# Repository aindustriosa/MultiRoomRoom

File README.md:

Multi Room Room é un sistema de audio inalámbrico multi-habitación baseado en ESP32, Squeezelite[(1)](#1-httpsgithubcomsle118squeezelite-esp32) e Lyrion[(2)](#2-httpsgithubcomlms-communityslimserver). Permite a implementación dun sistema de fío musical inalámbrico de baixo custo e con tecnoloxías abertas. Neste repositorio atópanse as listas de materiais, deseños de placas electrónicas e caixas así como as instruccións para a posta en marcha do sistema.

## Documentación

[Documentación en galego](./docs/gl/INDICE.md)

Documentation in English (In progress)

## Referencias

#### [(1) https://github.com/sle118/squeezelite-esp32](https://github.com/sle118/squeezelite-esp32)

#### [(2) https://github.com/lms-community/slimserver](https://github.com/lms-community/slimserver)

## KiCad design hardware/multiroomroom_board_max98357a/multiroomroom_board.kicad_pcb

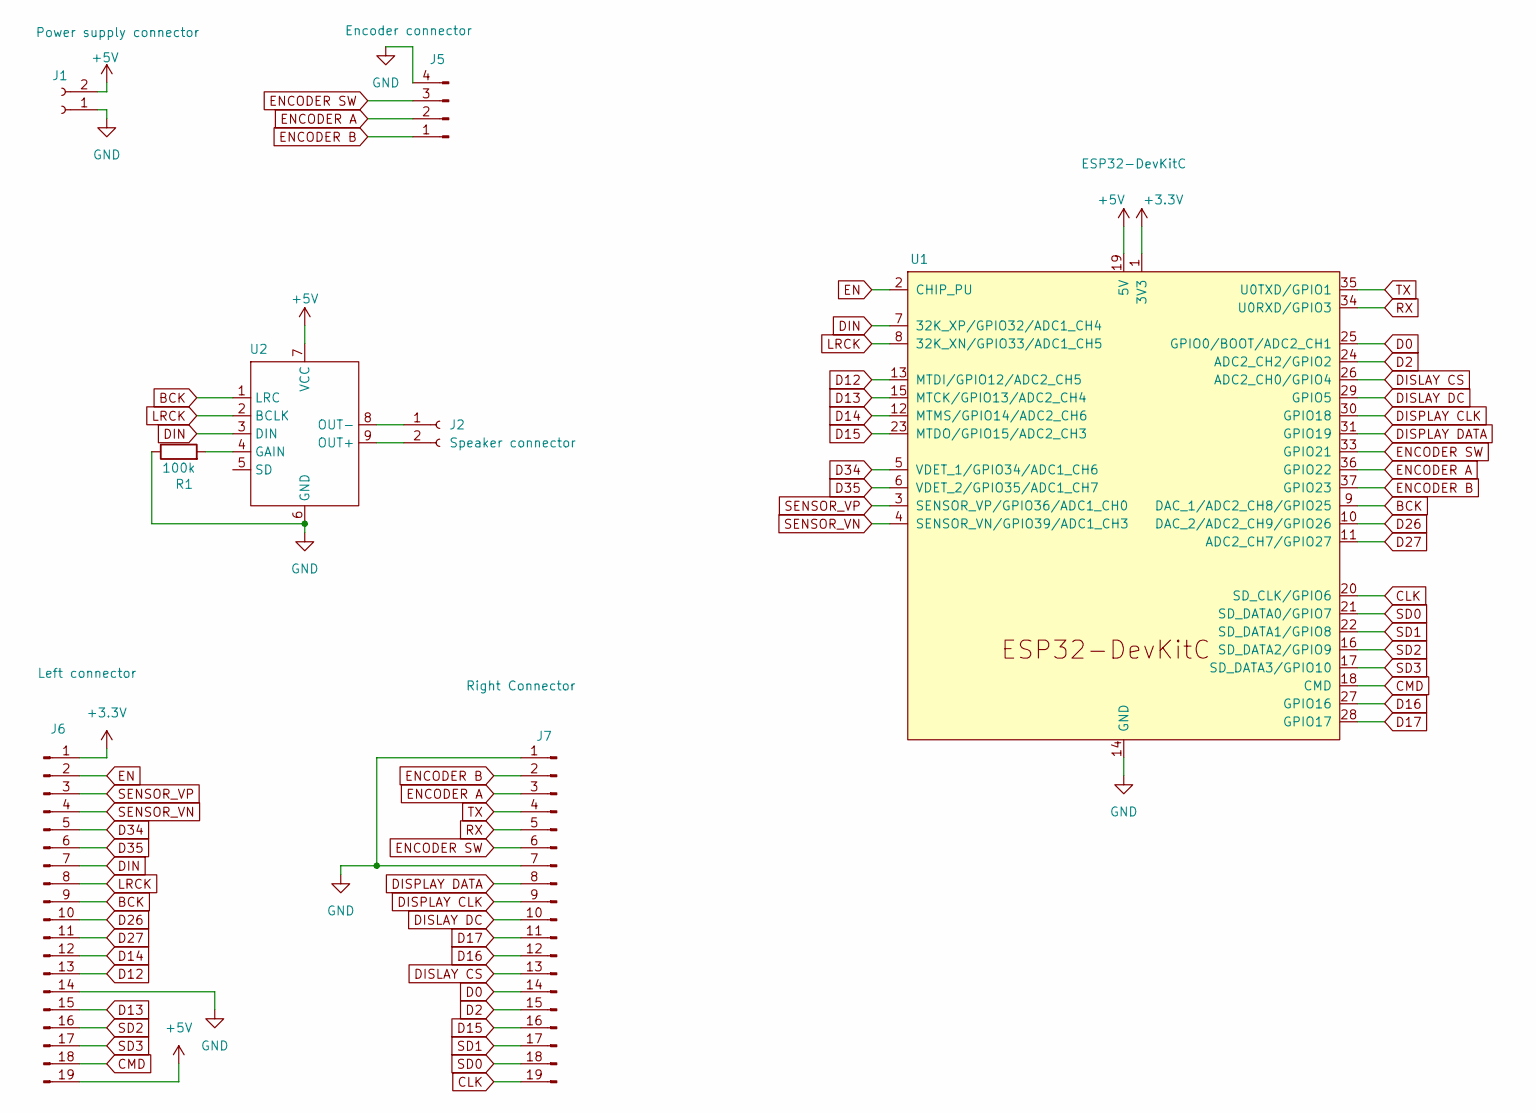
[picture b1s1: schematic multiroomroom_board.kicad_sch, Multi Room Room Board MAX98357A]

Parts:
J1: Power supply connector; JST_XH_B2B-XH-A_1x02_P2.50mm_Vertical
J2: Speaker connector; JST_XH_B2B-XH-A_1x02_P2.50mm_Vertical
J5: Encoder connector; JST_XH_B4B-XH-A_1x04_P2.50mm_Vertical
J6: Left connector; PinHeader_1x19_P2.54mm_Vertical
J7: Right Connector; PinHeader_1x19_P2.54mm_Vertical
R1: 100k; R_Axial_DIN0207_L6.3mm_D2.5mm_P7.62mm_Horizontal
U1: ESP32-DevKitC
U2: MAX98357A

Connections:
+3.3V: J6.1, U1.1 (3V3)
+5V: J1.2, J6.19, U1.19 (5V), U2.7 (VCC)
BCK: J6.9, U1.9 (DAC_1/ADC2_CH8/GPIO25), U2.1 (LRC)
CLK: J7.19, U1.20 (SD_CLK/GPIO6)
CMD: J6.18, U1.18 (CMD)
D0: J7.14, U1.25 (GPIO0/BOOT/ADC2_CH1)
D2: J7.15, U1.24 (ADC2_CH2/GPIO2)
D12: J6.13, U1.13 (MTDI/GPIO12/ADC2_CH5)
D13: J6.15, U1.15 (MTCK/GPIO13/ADC2_CH4)
D14: J6.12, U1.12 (MTMS/GPIO14/ADC2_CH6)
D15: J7.16, U1.23 (MTDO/GPIO15/ADC2_CH3)
D16: J7.12, U1.27 (GPIO16)
D17: J7.11, U1.28 (GPIO17)
D26: J6.10, U1.10 (DAC_2/ADC2_CH9/GPIO26)
D27: J6.11, U1.11 (ADC2_CH7/GPIO27)
D34: J6.5, U1.5 (VDET_1/GPIO34/ADC1_CH6)
D35: J6.6, U1.6 (VDET_2/GPIO35/ADC1_CH7)
DIN: J6.7, U1.7 (32K_XP/GPIO32/ADC1_CH4), U2.3 (DIN)
DISLAY CS: J7.13, U1.26 (ADC2_CH0/GPIO4)
DISLAY DC: J7.10, U1.29 (GPIO5)
DISPLAY CLK: J7.9, U1.30 (GPIO18)
DISPLAY DATA: J7.8, U1.31 (GPIO19)
EN: J6.2, U1.2 (CHIP_PU)
ENCODER A: J5.2, J7.3, U1.36 (GPIO22)
ENCODER B: J5.1, J7.2, U1.37 (GPIO23)
ENCODER SW: J5.3, J7.6, U1.33 (GPIO21)
GND: J1.1, J5.4, J6.14, J7.1, J7.7, R1.1, U1.14 (GND), U1.32 (GND), U1.38 (GND), U2.6 (GND)
LRCK: J6.8, U1.8 (32K_XN/GPIO33/ADC1_CH5), U2.2 (BCLK)
unnamed: J2.1, U2.8 (OUT-)
unnamed: J2.2, U2.9 (OUT+)
unnamed: R1.2, U2.4 (GAIN)
RX: J7.5, U1.34 (U0RXD/GPIO3)
SD0: J7.18, U1.21 (SD_DATA0/GPIO7)
SD1: J7.17, U1.22 (SD_DATA1/GPIO8)
SD2: J6.16, U1.16 (SD_DATA2/GPIO9)
SD3: J6.17, U1.17 (SD_DATA3/GPIO10)
SENSOR_VN: J6.4, U1.4 (SENSOR_VN/GPIO39/ADC1_CH3)
SENSOR_VP: J6.3, U1.3 (SENSOR_VP/GPIO36/ADC1_CH0)
TX: J7.4, U1.35 (U0TXD/GPIO1)

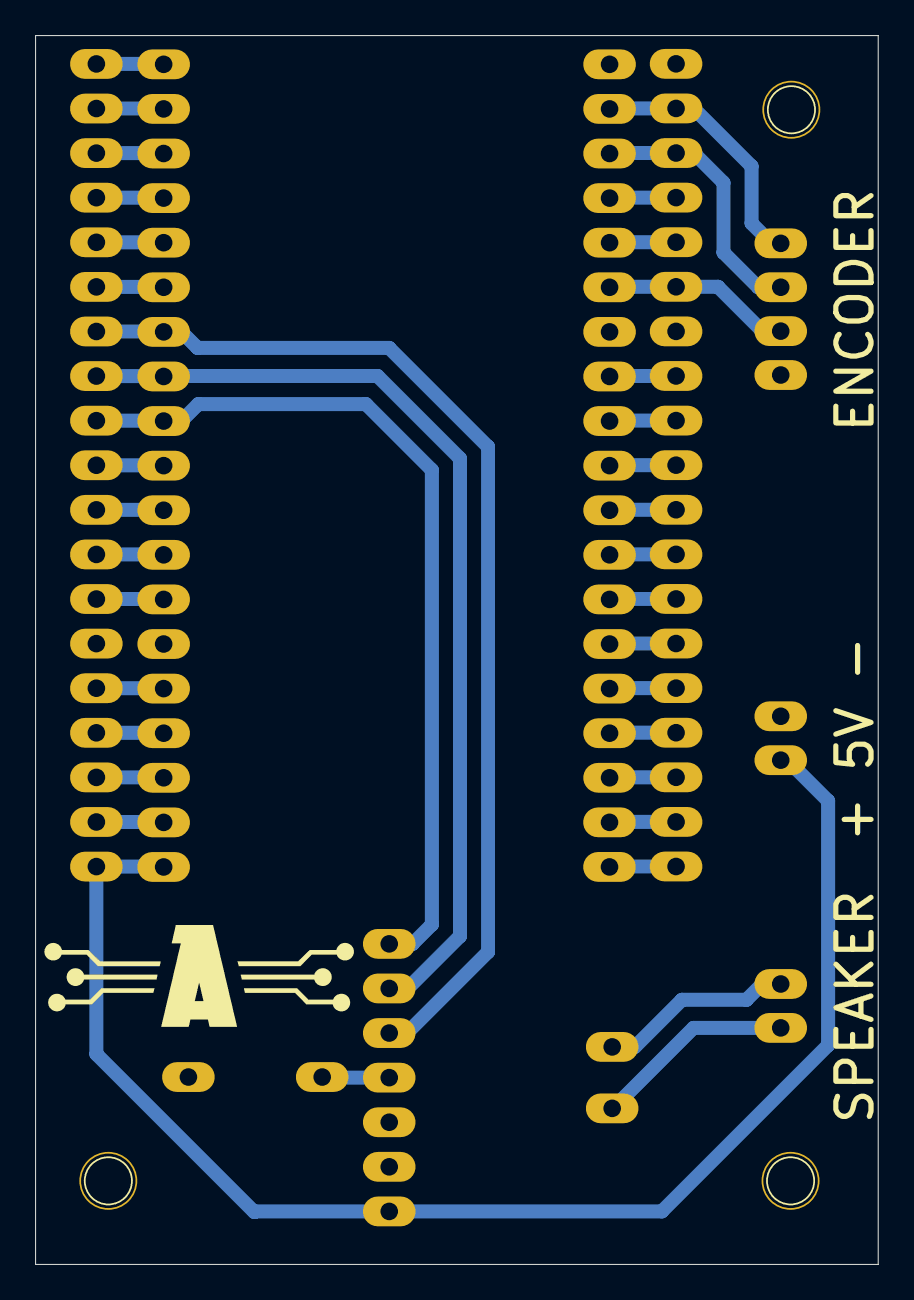
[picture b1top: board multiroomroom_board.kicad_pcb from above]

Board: 2 copper layers, 48.0 x 70.0 mm, 8 parts (0 on the bottom side), 39 nets.

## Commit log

2024-10-06 How to flash firmware
2024-10-06 Speaker box docs
